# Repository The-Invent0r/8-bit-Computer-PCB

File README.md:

# 8-bit-Computer-PCB

So a while back I decided to build an 8 bit breadboard computer using Ben Eater's excellent youtube tutorials. Needless to say I learned a lot about electronics, and even more so about troubleshooting issues that arise (which happened a lot!). Anyway long story short I was able to get the breadboard computer working. Recently, I decided to teach myself PCB design, and I thought, what better project to build than my 8 bit computer. After soldering all the components and powering it up I realized that none of the registers were latching any values. After about an hour of debugging I realized that I accidentally neglected to connect the CLR pins on the A and B registers and the ALU to the CLR pin on the Instruction Register (you'll notice this on the main hierarchy page of the schematic). Luckily that was the only issue, I fixed it by soldering a wire from the CLR pin on the B register to the CLR pin on the Instruction Register (as you can see on the back view of the PCB). If you want to build this PCB I attached all the files, I didn't fix the CLR connection on the design files though since I didn't have time to reroute and everything. If you have any questions feel free to message me on reddit which you can find a link to on my github profile.

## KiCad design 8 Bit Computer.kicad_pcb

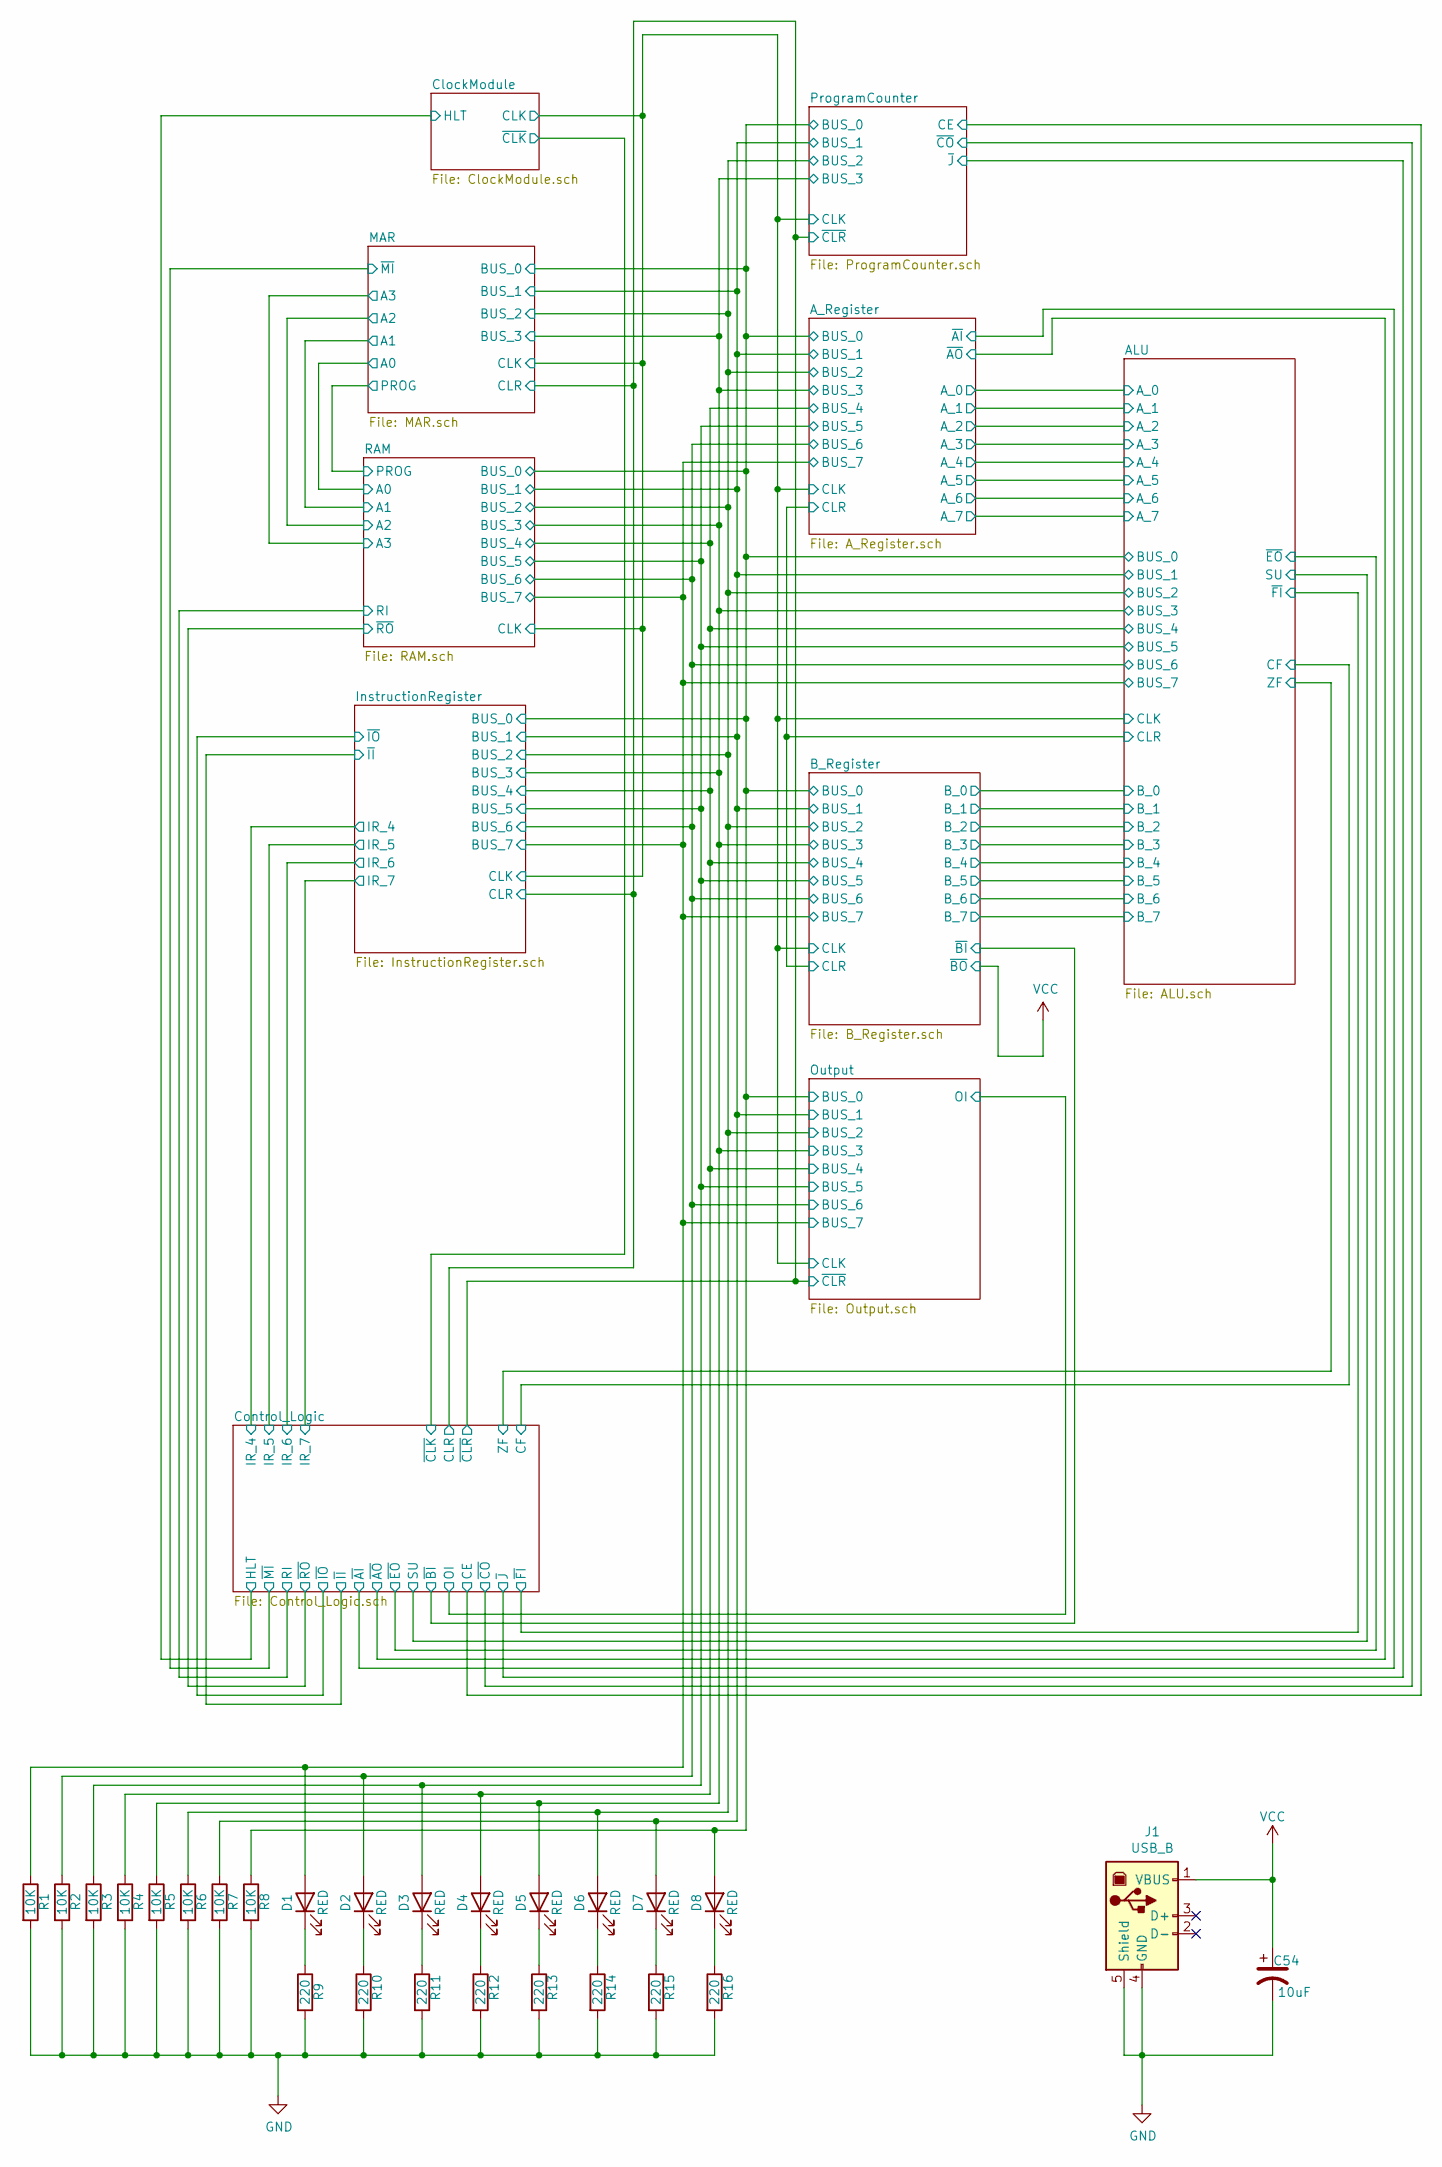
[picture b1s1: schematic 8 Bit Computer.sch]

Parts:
C54: 10uF; CP_Radial_D5.0mm_P2.00mm
D1, D2, D3, D4, D5, D6, D7, D8: RED; LED_D5.0mm
J1: USB_B; USB_B_OST_USB-B1HSxx_Horizontal
R1, R2, R3, R4, R5, R6, R7, R8: 10K; R_Axial_DIN0207_L6.3mm_D2.5mm_P7.62mm_Horizontal
R9, R10, R11, R12, R13, R14, R15, R16: 220; R_Axial_DIN0207_L6.3mm_D2.5mm_P7.62mm_Horizontal

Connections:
/ALU/BUS_0: D8.2 (A), R8.1; also elsewhere on the board
/ALU/BUS_1: D7.2 (A), R7.1; also elsewhere on the board
/ALU/BUS_2: D6.2 (A), R6.1; also elsewhere on the board
/ALU/BUS_3: D5.2 (A), R5.1; also elsewhere on the board
/ALU/BUS_4: D4.2 (A), R4.1; also elsewhere on the board
/ALU/BUS_5: D3.2 (A), R3.1; also elsewhere on the board
/ALU/BUS_6: D2.2 (A), R2.1; also elsewhere on the board
/ALU/BUS_7: D1.2 (A), R1.1; also elsewhere on the board
GND: C54.2, J1.4 (GND), J1.5 (Shield), R1.2, R2.2, R3.2, R4.2, R5.2, R6.2, R7.2, R8.2, R9.2, R10.2, R11.2, R12.2, R13.2, R14.2, R15.2, R16.2; also elsewhere on the board
unnamed: D1.1 (K), R9.1
unnamed: D2.1 (K), R10.1
unnamed: D3.1 (K), R11.1
unnamed: D4.1 (K), R12.1
unnamed: D5.1 (K), R13.1
unnamed: D6.1 (K), R14.1
unnamed: D7.1 (K), R15.1
unnamed: D8.1 (K), R16.1
VCC: C54.1, J1.1 (VBUS); also elsewhere on the board

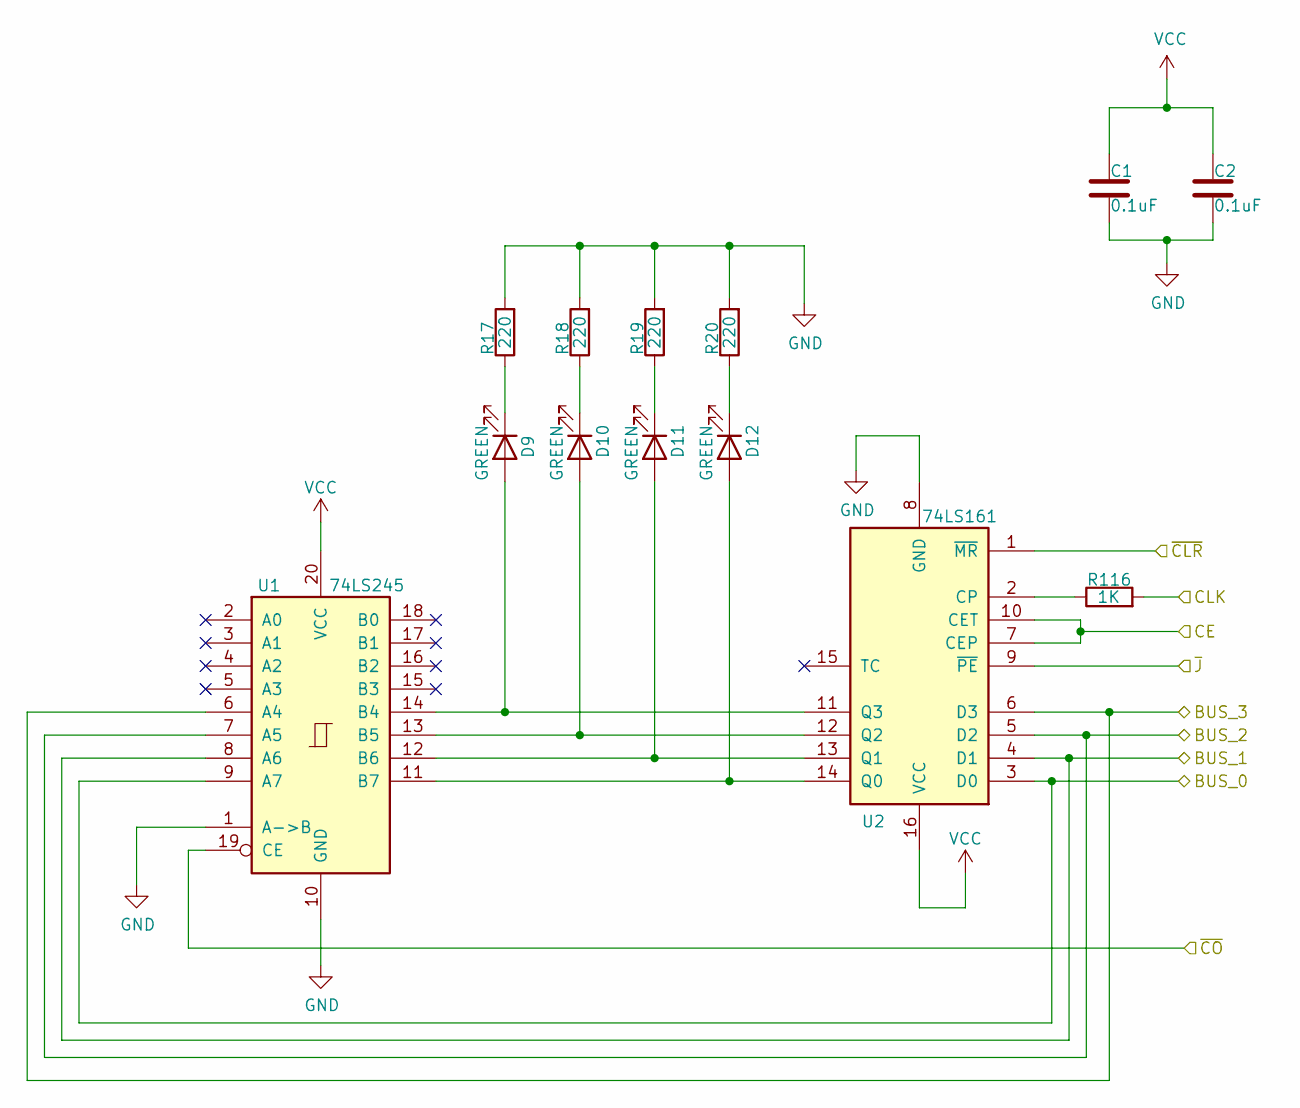
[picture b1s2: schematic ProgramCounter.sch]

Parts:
C1, C2: 0.1uF; C_Disc_D4.3mm_W1.9mm_P5.00mm
D9, D10, D11, D12: GREEN; LED_D5.0mm
R17, R18, R19, R20: 220; R_Axial_DIN0207_L6.3mm_D2.5mm_P7.62mm_Horizontal
R116: 1K; R_Axial_DIN0207_L6.3mm_D2.5mm_P7.62mm_Horizontal
U1: 74LS245; DIP-20_W7.62mm_Socket_LongPads
U2: 74LS161; DIP-16_W7.62mm_Socket_LongPads

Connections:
/ALU/BUS_0: U1.9 (A7), U2.3 (D0); also elsewhere on the board
/ALU/BUS_1: U1.8 (A6), U2.4 (D1); also elsewhere on the board
/ALU/BUS_2: U1.7 (A5), U2.5 (D2); also elsewhere on the board
/ALU/BUS_3: U1.6 (A4), U2.6 (D3); also elsewhere on the board
/ALU/CLK: R116.2; also elsewhere on the board
/Control_Logic/CE: U2.7 (CEP), U2.10 (CET); also elsewhere on the board
/Control_Logic/~CLR: U2.1 (~MR); also elsewhere on the board
/Control_Logic/~CO: U1.19 (CE); also elsewhere on the board
/Control_Logic/~J: U2.9 (~PE); also elsewhere on the board
GND: C1.2, C2.2, R17.2, R18.2, R19.2, R20.2, U1.1 (A->B), U1.10 (GND), U2.8 (GND); also elsewhere on the board
unnamed: D9.1 (K), R17.1
unnamed: D9.2 (A), U1.14 (B4), U2.11 (Q3)
unnamed: D10.1 (K), R18.1
unnamed: D10.2 (A), U1.13 (B5), U2.12 (Q2)
unnamed: D11.1 (K), R19.1
unnamed: D11.2 (A), U1.12 (B6), U2.13 (Q1)
unnamed: D12.1 (K), R20.1
unnamed: D12.2 (A), U1.11 (B7), U2.14 (Q0)
unnamed: R116.1, U2.2 (CP)
VCC: C1.1, C2.1, U1.20 (VCC), U2.16 (VCC); also elsewhere on the board

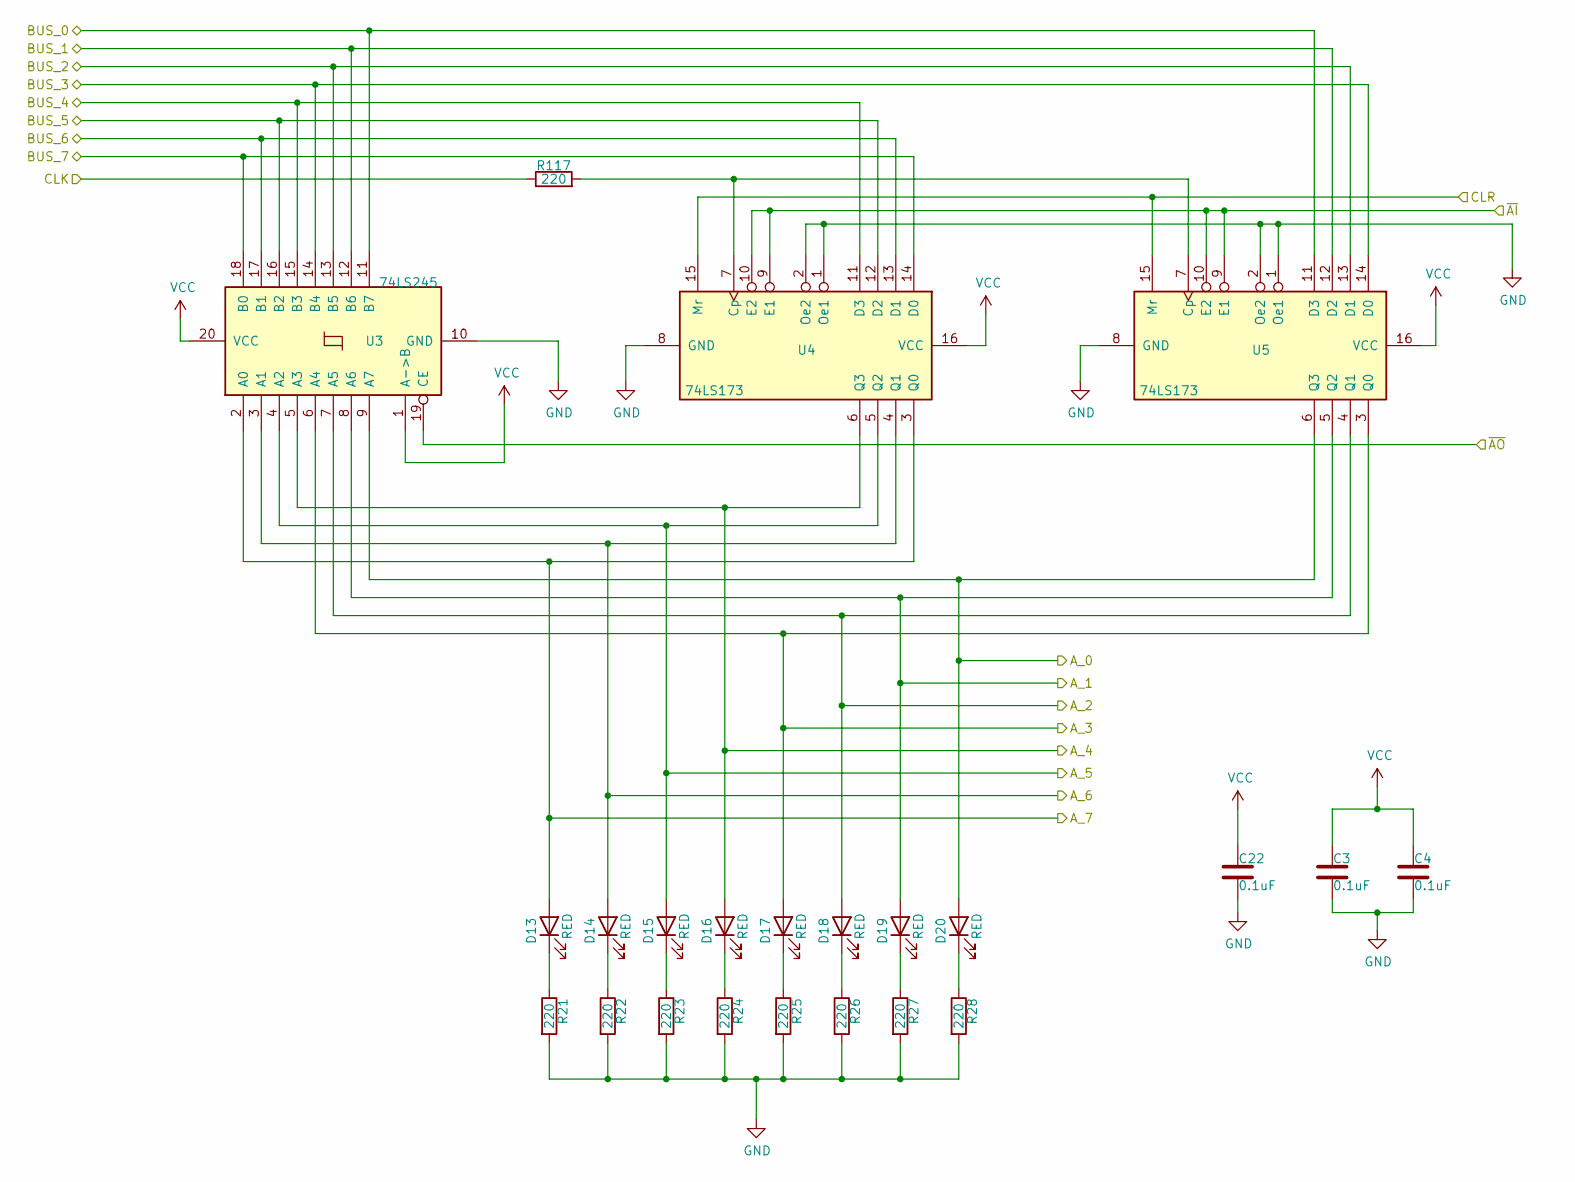
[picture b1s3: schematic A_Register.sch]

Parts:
C3, C4, C22: 0.1uF; C_Disc_D4.3mm_W1.9mm_P5.00mm
D13, D14, D15, D16, D17, D18, D19, D20: RED; LED_D5.0mm
R21, R22, R23, R24, R25, R26, R27, R28, R117: 220; R_Axial_DIN0207_L6.3mm_D2.5mm_P7.62mm_Horizontal
U3: 74LS245; DIP-20_W7.62mm_Socket_LongPads
U4, U5: 74LS173; DIP-16_W7.62mm_Socket_LongPads

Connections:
/ALU/A_0: D20.2 (A), U3.9 (A7), U5.6 (Q3); also elsewhere on the board
/ALU/A_1: D19.2 (A), U3.8 (A6), U5.5 (Q2); also elsewhere on the board
/ALU/A_2: D18.2 (A), U3.7 (A5), U5.4 (Q1); also elsewhere on the board
/ALU/A_3: D17.2 (A), U3.6 (A4), U5.3 (Q0); also elsewhere on the board
/ALU/A_4: D16.2 (A), U3.5 (A3), U4.6 (Q3); also elsewhere on the board
/ALU/A_5: D15.2 (A), U3.4 (A2), U4.5 (Q2); also elsewhere on the board
/ALU/A_6: D14.2 (A), U3.3 (A1), U4.4 (Q1); also elsewhere on the board
/ALU/A_7: D13.2 (A), U3.2 (A0), U4.3 (Q0); also elsewhere on the board
/ALU/BUS_0: U3.11 (B7), U5.11 (D3); also elsewhere on the board
/ALU/BUS_1: U3.12 (B6), U5.12 (D2); also elsewhere on the board
/ALU/BUS_2: U3.13 (B5), U5.13 (D1); also elsewhere on the board
/ALU/BUS_3: U3.14 (B4), U5.14 (D0); also elsewhere on the board
/ALU/BUS_4: U3.15 (B3), U4.11 (D3); also elsewhere on the board
/ALU/BUS_5: U3.16 (B2), U4.12 (D2); also elsewhere on the board
/ALU/BUS_6: U3.17 (B1), U4.13 (D1); also elsewhere on the board
/ALU/BUS_7: U3.18 (B0), U4.14 (D0); also elsewhere on the board
/ALU/CLK: R117.1; also elsewhere on the board
/ALU/CLR: U4.15 (Mr), U5.15 (Mr); also elsewhere on the board
/A_Register/~AI: U4.9 (E1), U4.10 (E2), U5.9 (E1), U5.10 (E2); also elsewhere on the board
/A_Register/~AO: U3.19 (CE); also elsewhere on the board
GND: C3.2, C4.2, C22.2, R21.2, R22.2, R23.2, R24.2, R25.2, R26.2, R27.2, R28.2, U3.10 (GND), U4.1 (Oe1), U4.2 (Oe2), U4.8 (GND), U5.1 (Oe1), U5.2 (Oe2), U5.8 (GND); also elsewhere on the board
unnamed: D13.1 (K), R21.1
unnamed: D14.1 (K), R22.1
unnamed: D15.1 (K), R23.1
unnamed: D16.1 (K), R24.1
unnamed: D17.1 (K), R25.1
unnamed: D18.1 (K), R26.1
unnamed: D19.1 (K), R27.1
unnamed: D20.1 (K), R28.1
unnamed: R117.2, U4.7 (Cp), U5.7 (Cp)
VCC: C3.1, C4.1, C22.1, U3.1 (A->B), U3.20 (VCC), U4.16 (VCC), U5.16 (VCC); also elsewhere on the board

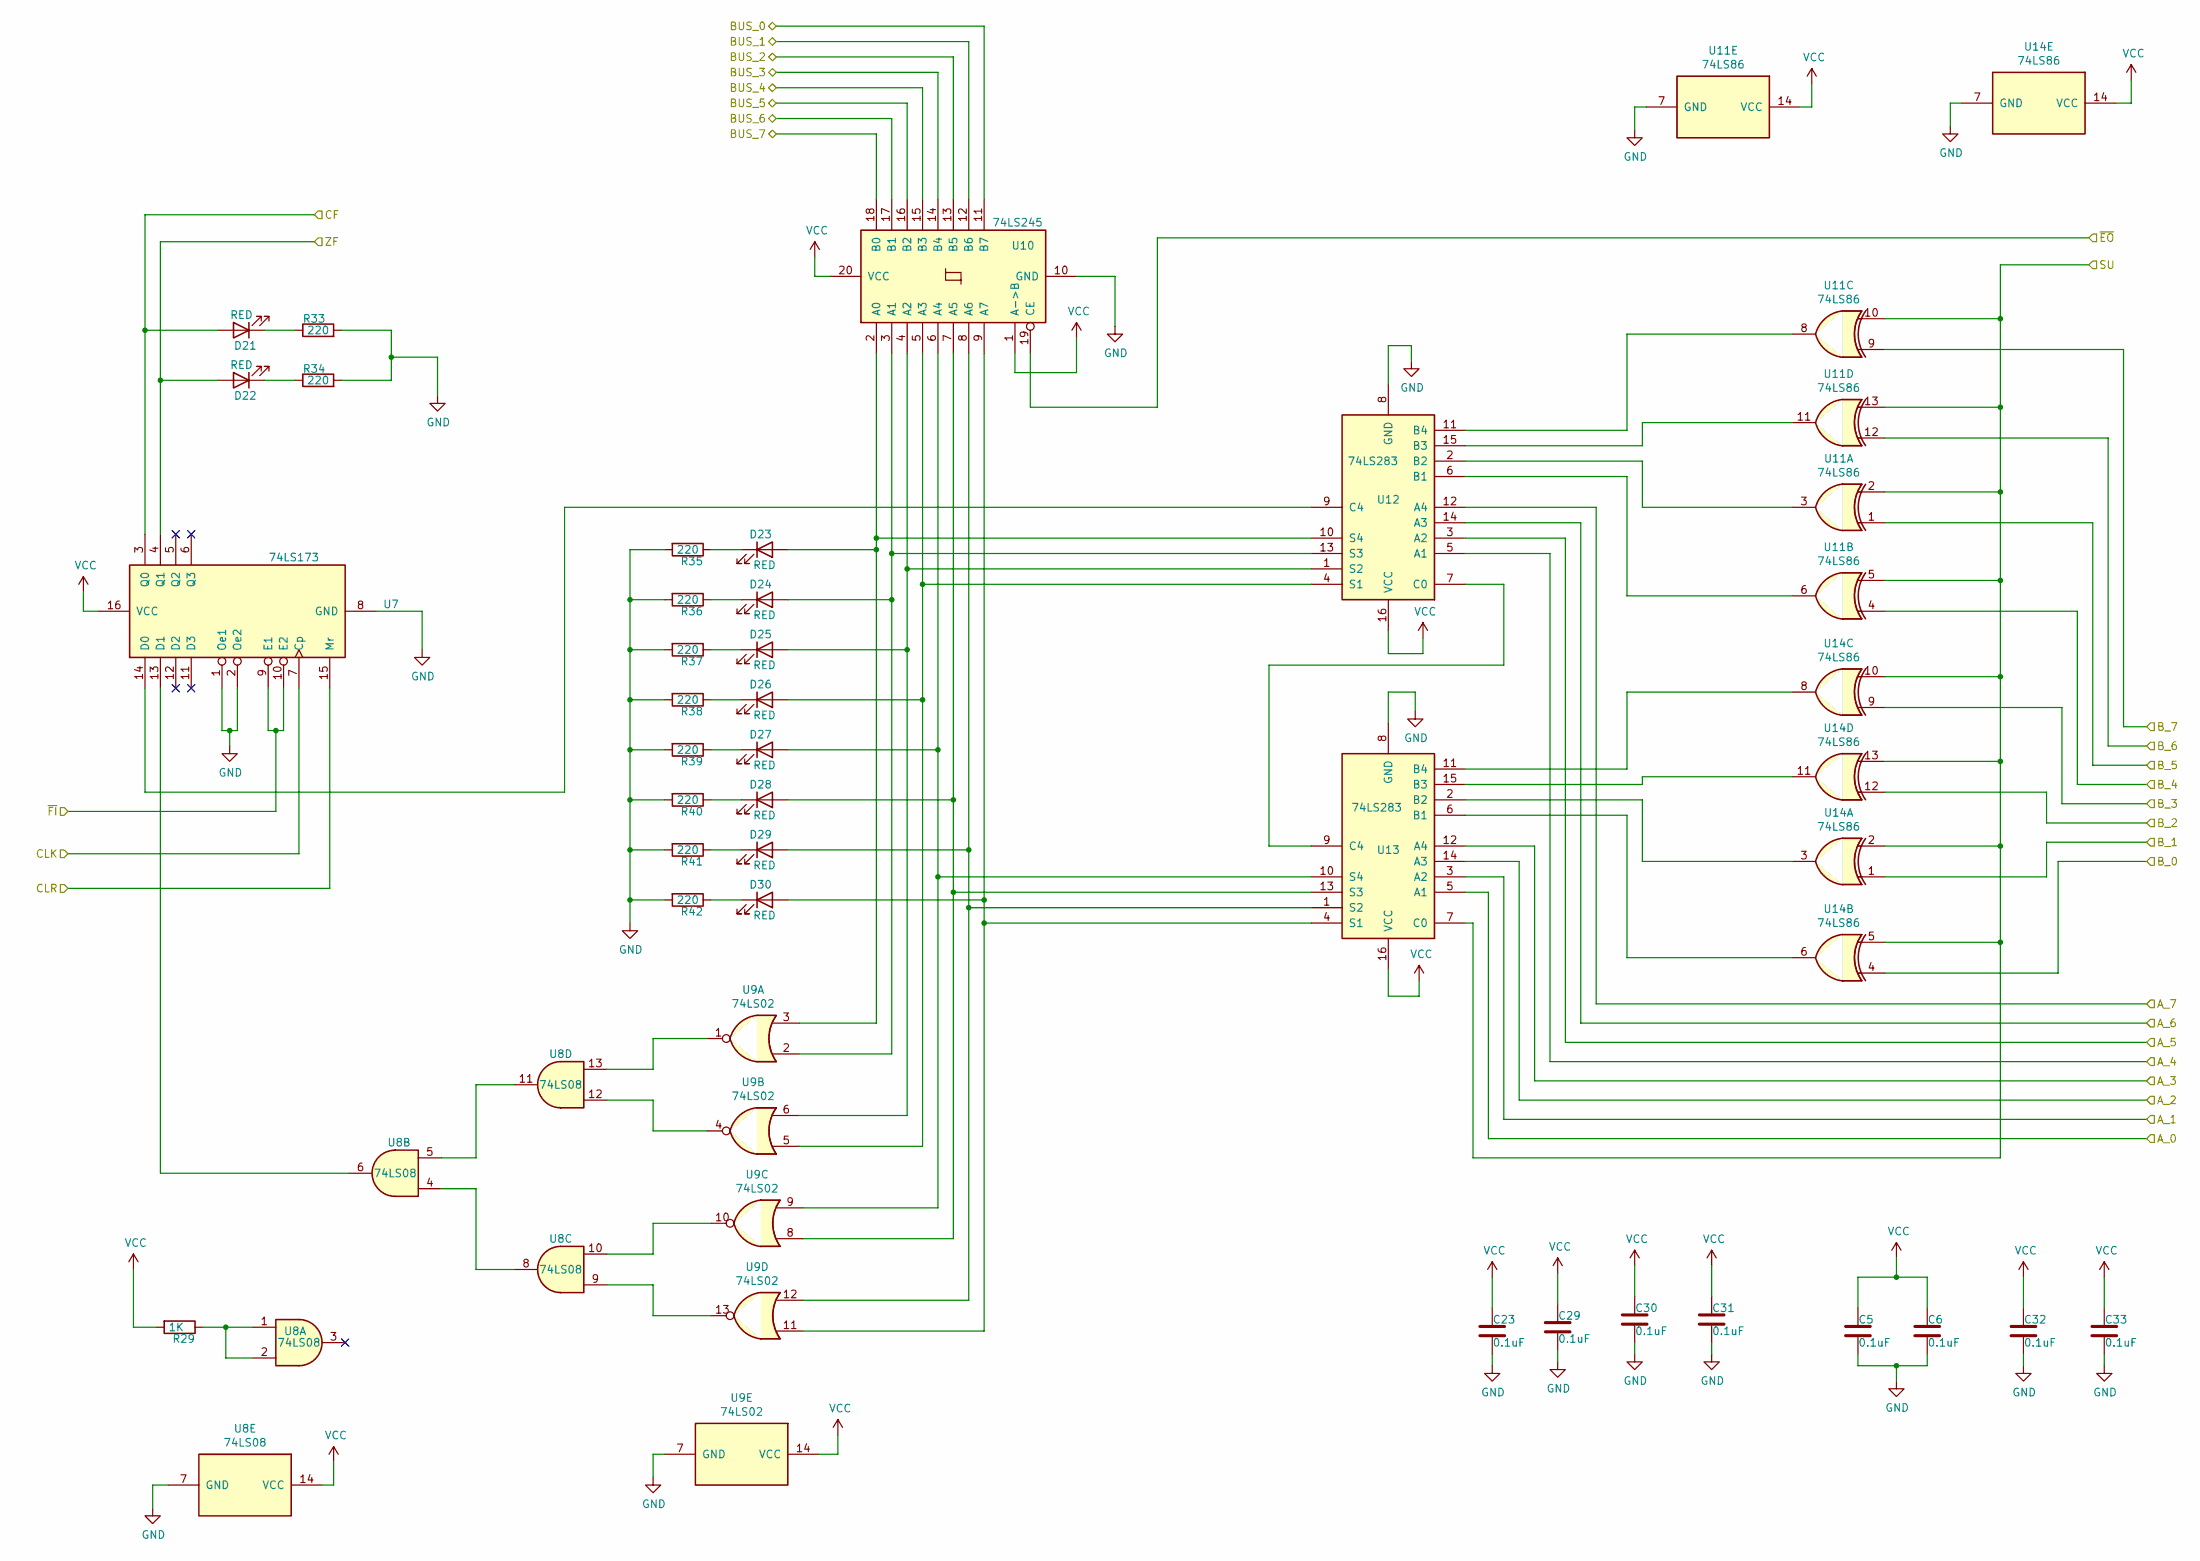
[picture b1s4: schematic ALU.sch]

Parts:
C5, C6, C23, C29, C30, C31, C32, C33: 0.1uF; C_Disc_D4.3mm_W1.9mm_P5.00mm
D21, D22, D23, D24, D25, D26, D27, D28, D29, D30: RED; LED_D5.0mm
R29: 1K; R_Axial_DIN0207_L6.3mm_D2.5mm_P7.62mm_Horizontal
R33, R34, R35, R36, R37, R38, R39, R40, R41, R42: 220; R_Axial_DIN0207_L6.3mm_D2.5mm_P7.62mm_Horizontal
U7: 74LS173; DIP-16_W7.62mm_Socket_LongPads
U8: 74LS08; DIP-14_W7.62mm_Socket_LongPads
U9: 74LS02; DIP-14_W7.62mm_Socket_LongPads
U10: 74LS245; DIP-20_W7.62mm_Socket_LongPads
U11, U14: 74LS86; DIP-14_W7.62mm_Socket_LongPads
U12, U13: 74LS283; DIP-16_W7.62mm_Socket_LongPads

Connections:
/ALU/A_0: U13.5 (A1); also elsewhere on the board
/ALU/A_1: U13.3 (A2); also elsewhere on the board
/ALU/A_2: U13.14 (A3); also elsewhere on the board
/ALU/A_3: U13.12 (A4); also elsewhere on the board
/ALU/A_4: U12.5 (A1); also elsewhere on the board
/ALU/A_5: U12.3 (A2); also elsewhere on the board
/ALU/A_6: U12.14 (A3); also elsewhere on the board
/ALU/A_7: U12.12 (A4); also elsewhere on the board
/ALU/BUS_0: U10.11 (B7); also elsewhere on the board
/ALU/BUS_1: U10.12 (B6); also elsewhere on the board
/ALU/BUS_2: U10.13 (B5); also elsewhere on the board
/ALU/BUS_3: U10.14 (B4); also elsewhere on the board
/ALU/BUS_4: U10.15 (B3); also elsewhere on the board
/ALU/BUS_5: U10.16 (B2); also elsewhere on the board
/ALU/BUS_6: U10.17 (B1); also elsewhere on the board
/ALU/BUS_7: U10.18 (B0); also elsewhere on the board
/ALU/B_0: U14.4; also elsewhere on the board
/ALU/B_1: U14.1; also elsewhere on the board
/ALU/B_2: U14.12; also elsewhere on the board
/ALU/B_3: U14.9; also elsewhere on the board
/ALU/B_4: U11.4; also elsewhere on the board
/ALU/B_5: U11.1; also elsewhere on the board
/ALU/B_6: U11.12; also elsewhere on the board
/ALU/B_7: U11.9; also elsewhere on the board
/ALU/CF: D21.2 (A), U7.3 (Q0); also elsewhere on the board
/ALU/CLK: U7.7 (Cp); also elsewhere on the board
/ALU/CLR: U7.15 (Mr); also elsewhere on the board
/ALU/SU: U11.2, U11.5, U11.10, U11.13, U13.7 (C0), U14.2, U14.5, U14.10, U14.13; also elsewhere on the board
/ALU/ZF: D22.2 (A), U7.4 (Q1); also elsewhere on the board
/ALU/~EO: U10.19 (CE); also elsewhere on the board
/ALU/~FI: U7.9 (E1), U7.10 (E2); also elsewhere on the board
GND: C5.2, C6.2, C23.2, C29.2, C30.2, C31.2, C32.2, C33.2, R33.2, R34.2, R35.2, R36.2, R37.2, R38.2, R39.2, R40.2, R41.2, R42.2, U7.1 (Oe1), U7.2 (Oe2), U7.8 (GND), U8.7 (GND), U9.7 (GND), U10.10 (GND), U11.7 (GND), U12.8 (GND), U13.8 (GND), U14.7 (GND); also elsewhere on the board
unnamed: D21.1 (K), R33.1
unnamed: D22.1 (K), R34.1
unnamed: D23.1 (K), R35.1
unnamed: D23.2 (A), U9.3, U10.2 (A0), U12.10 (S4)
unnamed: D24.1 (K), R36.1
unnamed: D24.2 (A), U9.2, U10.3 (A1), U12.13 (S3)
unnamed: D25.1 (K), R37.1
unnamed: D25.2 (A), U9.6, U10.4 (A2), U12.1 (S2)
unnamed: D26.1 (K), R38.1
unnamed: D26.2 (A), U9.5, U10.5 (A3), U12.4 (S1)
unnamed: D27.1 (K), R39.1
unnamed: D27.2 (A), U9.9, U10.6 (A4), U13.10 (S4)
unnamed: D28.1 (K), R40.1
unnamed: D28.2 (A), U9.8, U10.7 (A5), U13.13 (S3)
unnamed: D29.1 (K), R41.1
unnamed: D29.2 (A), U9.12, U10.8 (A6), U13.1 (S2)
unnamed: D30.1 (K), R42.1
unnamed: D30.2 (A), U9.11, U10.9 (A7), U13.4 (S1)
unnamed: R29.1, U8.1, U8.2
unnamed: U7.13 (D1), U8.6
unnamed: U8.4, U8.8
unnamed: U8.9, U9.13
unnamed: U8.10, U9.10
unnamed: U8.5, U8.11
unnamed: U8.12, U9.4
unnamed: U8.13, U9.1
unnamed: U11.3, U12.2 (B2)
unnamed: U11.6, U12.6 (B1)
unnamed: U11.8, U12.11 (B4)
unnamed: U11.11, U12.15 (B3)
unnamed: U12.7 (C0), U13.9 (C4)
unnamed: U7.14 (D0), U12.9 (C4)
unnamed: U13.2 (B2), U14.3
unnamed: U13.6 (B1), U14.6
unnamed: U13.11 (B4), U14.8
unnamed: U13.15 (B3), U14.11
VCC: C5.1, C6.1, C23.1, C29.1, C30.1, C31.1, C32.1, C33.1, R29.2, U7.16 (VCC), U8.14 (VCC), U9.14 (VCC), U10.1 (A->B), U10.20 (VCC), U11.14 (VCC), U12.16 (VCC), U13.16 (VCC), U14.14 (VCC); also elsewhere on the board

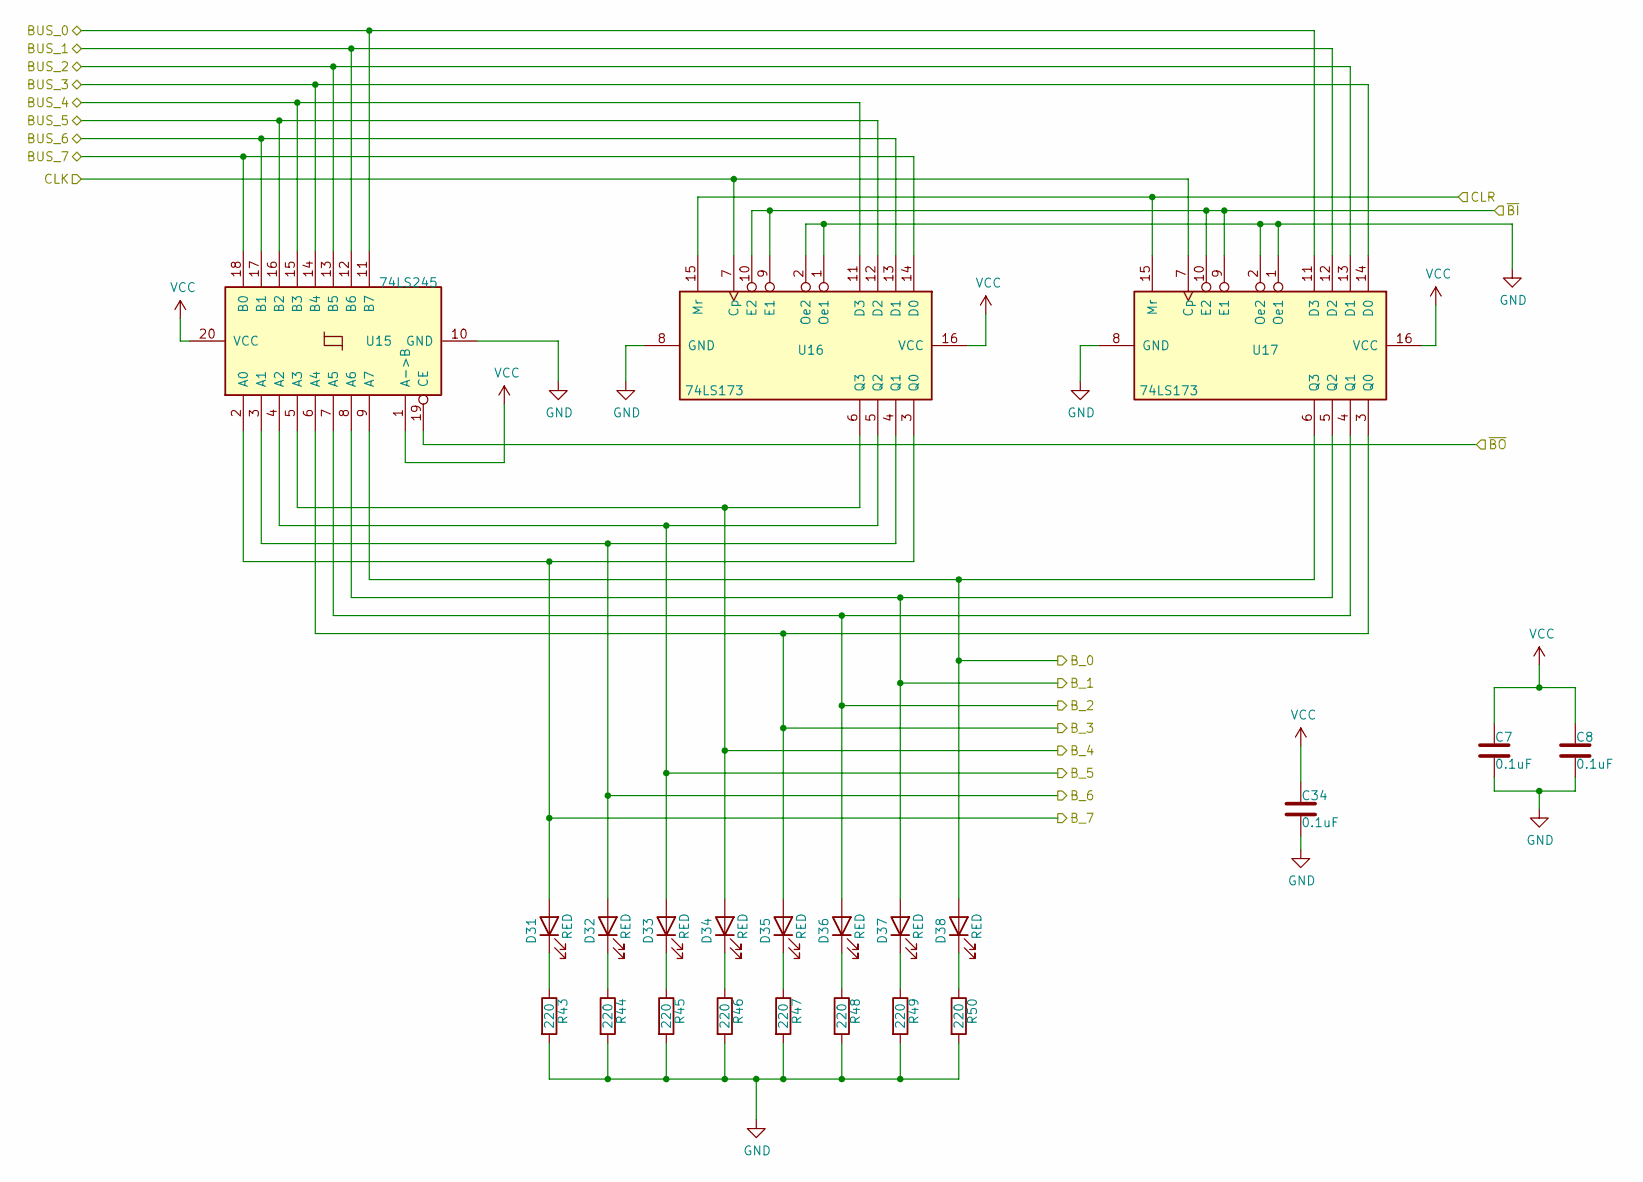
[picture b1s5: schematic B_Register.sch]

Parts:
C7, C8, C34: 0.1uF; C_Disc_D4.3mm_W1.9mm_P5.00mm
D31, D32, D33, D34, D35, D36, D37, D38: RED; LED_D5.0mm
R43, R44, R45, R46, R47, R48, R49, R50: 220; R_Axial_DIN0207_L6.3mm_D2.5mm_P7.62mm_Horizontal
U15: 74LS245; DIP-20_W7.62mm_Socket_LongPads
U16, U17: 74LS173; DIP-16_W7.62mm_Socket_LongPads

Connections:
/ALU/BUS_0: U15.11 (B7), U17.11 (D3); also elsewhere on the board
/ALU/BUS_1: U15.12 (B6), U17.12 (D2); also elsewhere on the board
/ALU/BUS_2: U15.13 (B5), U17.13 (D1); also elsewhere on the board
/ALU/BUS_3: U15.14 (B4), U17.14 (D0); also elsewhere on the board
/ALU/BUS_4: U15.15 (B3), U16.11 (D3); also elsewhere on the board
/ALU/BUS_5: U15.16 (B2), U16.12 (D2); also elsewhere on the board
/ALU/BUS_6: U15.17 (B1), U16.13 (D1); also elsewhere on the board
/ALU/BUS_7: U15.18 (B0), U16.14 (D0); also elsewhere on the board
/ALU/B_0: D38.2 (A), U15.9 (A7), U17.6 (Q3); also elsewhere on the board
/ALU/B_1: D37.2 (A), U15.8 (A6), U17.5 (Q2); also elsewhere on the board
/ALU/B_2: D36.2 (A), U15.7 (A5), U17.4 (Q1); also elsewhere on the board
/ALU/B_3: D35.2 (A), U15.6 (A4), U17.3 (Q0); also elsewhere on the board
/ALU/B_4: D34.2 (A), U15.5 (A3), U16.6 (Q3); also elsewhere on the board
/ALU/B_5: D33.2 (A), U15.4 (A2), U16.5 (Q2); also elsewhere on the board
/ALU/B_6: D32.2 (A), U15.3 (A1), U16.4 (Q1); also elsewhere on the board
/ALU/B_7: D31.2 (A), U15.2 (A0), U16.3 (Q0); also elsewhere on the board
/ALU/CLK: U16.7 (Cp), U17.7 (Cp); also elsewhere on the board
/ALU/CLR: U16.15 (Mr), U17.15 (Mr); also elsewhere on the board
/B_Register/~BI: U16.9 (E1), U16.10 (E2), U17.9 (E1), U17.10 (E2); also elsewhere on the board
GND: C7.2, C8.2, C34.2, R43.2, R44.2, R45.2, R46.2, R47.2, R48.2, R49.2, R50.2, U15.10 (GND), U16.1 (Oe1), U16.2 (Oe2), U16.8 (GND), U17.1 (Oe1), U17.2 (Oe2), U17.8 (GND); also elsewhere on the board
unnamed: D31.1 (K), R43.1
unnamed: D32.1 (K), R44.1
unnamed: D33.1 (K), R45.1
unnamed: D34.1 (K), R46.1
unnamed: D35.1 (K), R47.1
unnamed: D36.1 (K), R48.1
unnamed: D37.1 (K), R49.1
unnamed: D38.1 (K), R50.1
VCC: C7.1, C8.1, C34.1, U15.1 (A->B), U15.19 (CE), U15.20 (VCC), U16.16 (VCC), U17.16 (VCC); also elsewhere on the board
